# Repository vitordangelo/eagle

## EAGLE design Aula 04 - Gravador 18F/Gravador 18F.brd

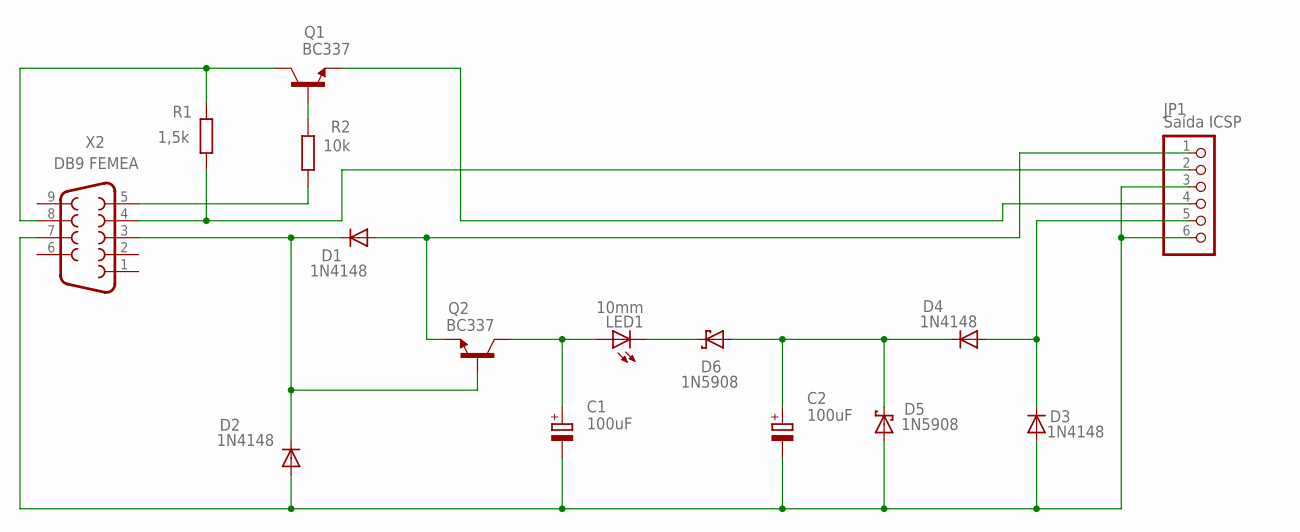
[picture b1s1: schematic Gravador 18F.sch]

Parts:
C1, C2: 100uF; E3,5-10
D1, D2, D3, D4: 1N4148; DO35-7
D5, D6: 1N5908; C4111-15
JP1: Saída ICSP; 1X06
LED1: 10mm; LED10MM
Q1, Q2: BC337; TO92
R1: 1,5k; 0207/7
R2: 10k; 0207/7
X2: DB9 FEMEA; F09HP

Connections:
unnamed: Q1.3 (C), R1.2, X2.8
unnamed: JP1.2, R1.1, X2.4
unnamed: Q1.2 (B), R2.2
unnamed: R2.1, X2.5
unnamed: C1.-, C2.-, D2.A, D3.A, D5.A, JP1.3, JP1.6, X2.7
unnamed: D1.C, D2.C, Q2.2 (B), X2.3
unnamed: C1.+, LED1.A, Q2.3 (C)
unnamed: D1.A, JP1.1, Q2.1 (E)
unnamed: D6.C, LED1.K (C)
unnamed: C2.+, D4.C, D5.C, D6.A
unnamed: D3.C, D4.A, JP1.5
unnamed: JP1.4, Q1.1 (E)

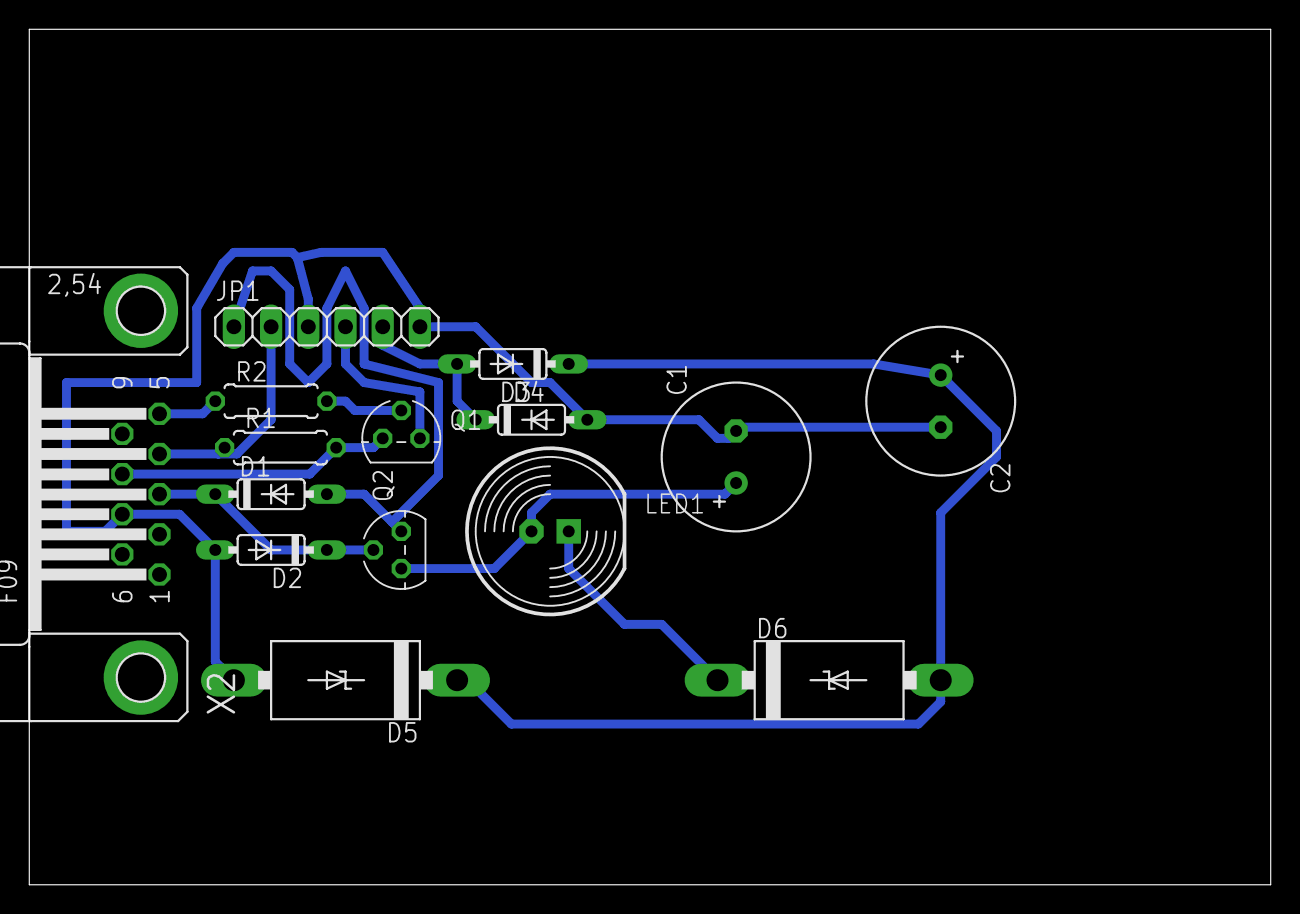
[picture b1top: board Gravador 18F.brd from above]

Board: 2 copper layers, 84.8 x 58.4 mm, 15 parts (0 on the bottom side), 12 nets.

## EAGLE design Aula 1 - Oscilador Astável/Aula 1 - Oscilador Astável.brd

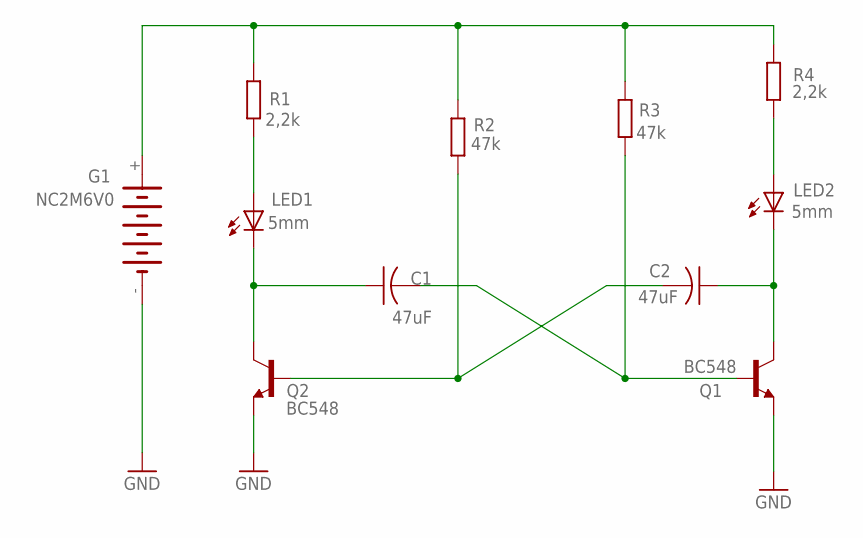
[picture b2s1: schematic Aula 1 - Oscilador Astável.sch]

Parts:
C1, C2: 47uF; C025-025X050
G1: NC2M6V0; NC2M
LED1, LED2: 5mm; LED5MM
Q1, Q2: BC548; TO92-EBC
R1, R4: 2,2k; 0204/5
R2, R3: 47k; 0204/5

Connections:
GND: G1.-, Q1.E, Q2.E
unnamed: LED1.A, R1.1
unnamed: G1.+, R1.2, R2.2, R3.2, R4.2
unnamed: LED2.A, R4.1
unnamed: C1.1, LED1.K (C), Q2.C
unnamed: C2.1, LED2.K (C), Q1.C
unnamed: C2.2, Q2.B, R2.1
unnamed: C1.2, Q1.B, R3.1

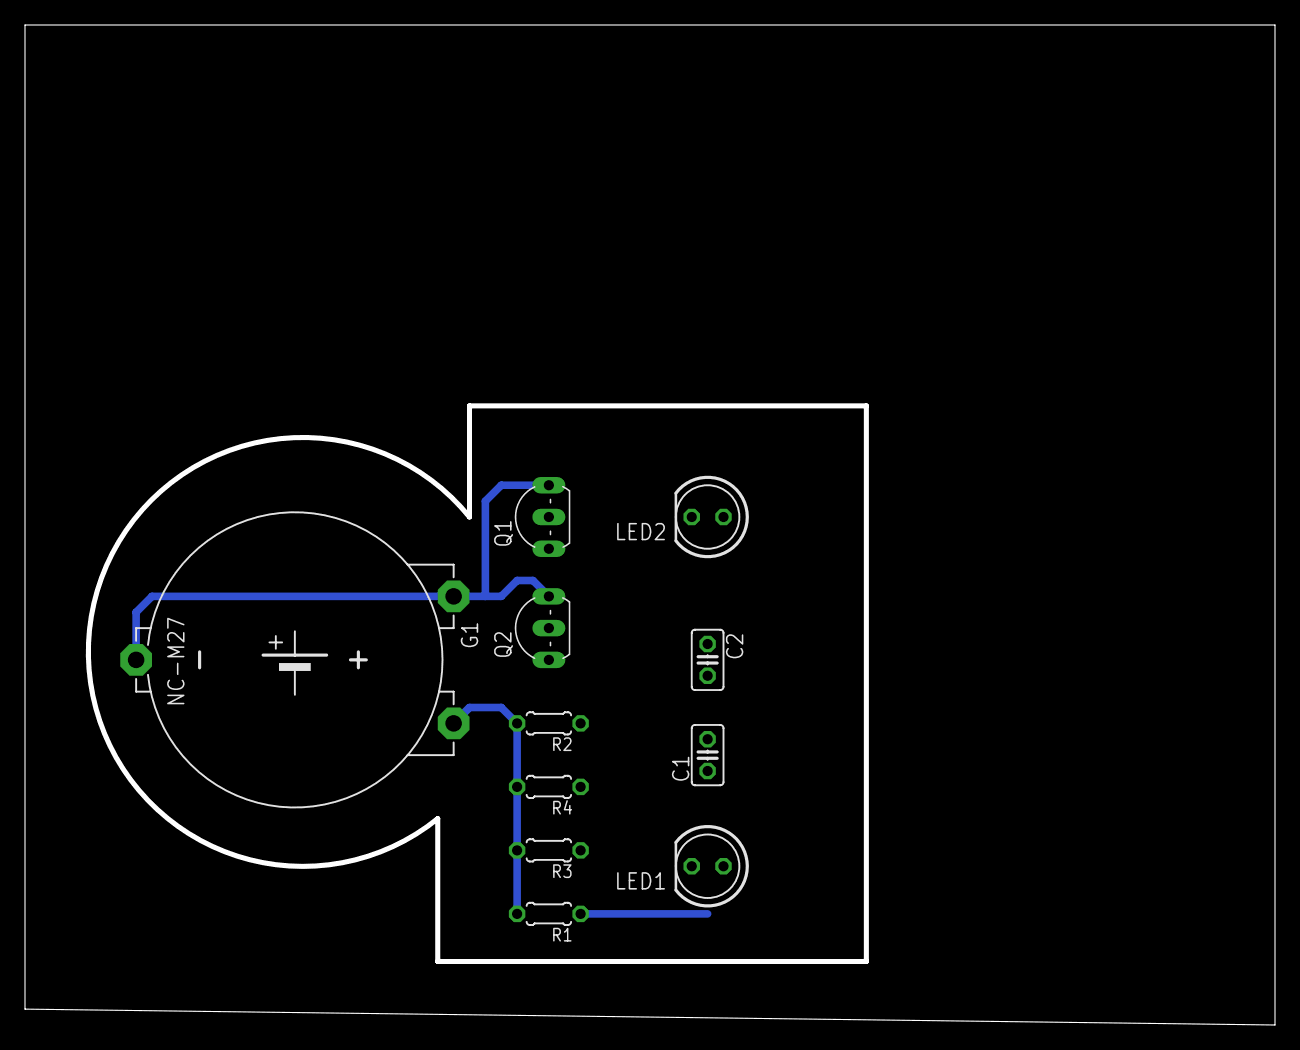
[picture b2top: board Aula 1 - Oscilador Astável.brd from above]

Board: 2 copper layers, 100.0 x 80.0 mm, 11 parts (0 on the bottom side), 8 nets.

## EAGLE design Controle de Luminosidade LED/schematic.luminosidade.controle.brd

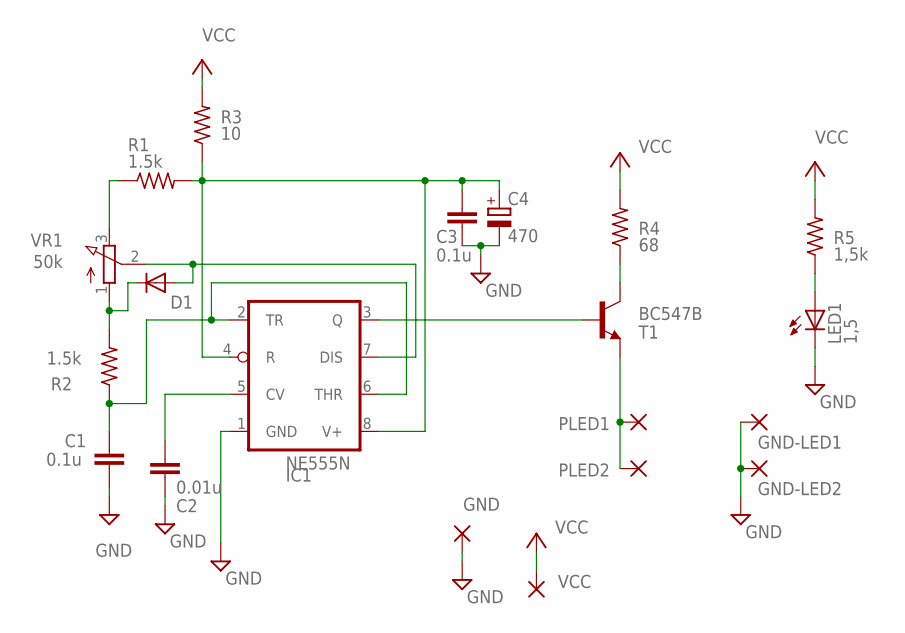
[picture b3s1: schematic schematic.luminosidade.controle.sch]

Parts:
C1, C3: 0.1u; C025-024X044
C2: 0.01u; C025-024X044
C4: 470; E3,5-10
D1: 1N4148DO35-7; DO35-7
GND: ET1; 2,15/1,0
GND-LED1, GND-LED2: GPAD; 2,15/1,0
IC1: NE555N; DIL08
LED1: 1,5; LED5MM
PLED1, PLED2: ET1; 2,15/1,0
R1, R2: 1.5k; 0204/5
R3: 10; 0204/5
R4: 68; 0204/5
R5: 1,5k; 0204/5
T1: BC547B; TO92
VCC: ET1; 2,15/1,0
VR1: 50k; 3RP/1610N

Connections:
GND: C1.2, C2.2, C3.2, C4.-, GND.1, GND-LED1.1, GND-LED2.1, IC1.1 (GND), LED1.K (C)
unnamed: C1.1, IC1.2 (TR), IC1.6 (THR), R2.1
unnamed: D1.C, R2.2, VR1.1 (A)
unnamed: D1.A, IC1.7 (DIS), VR1.2 (S)
unnamed: C2.1, IC1.5 (CV)
unnamed: R1.1, VR1.3 (E)
unnamed: IC1.3 (Q), T1.2 (B)
unnamed: C3.1, C4.+, IC1.4 (R), IC1.8 (V+), R1.2, R3.1
unnamed: R4.1, T1.3 (C)
unnamed: LED1.A, R5.1
unnamed: PLED1.1, PLED2.1, T1.1 (E)
VCC: R3.2, R4.2, R5.2, VCC.1

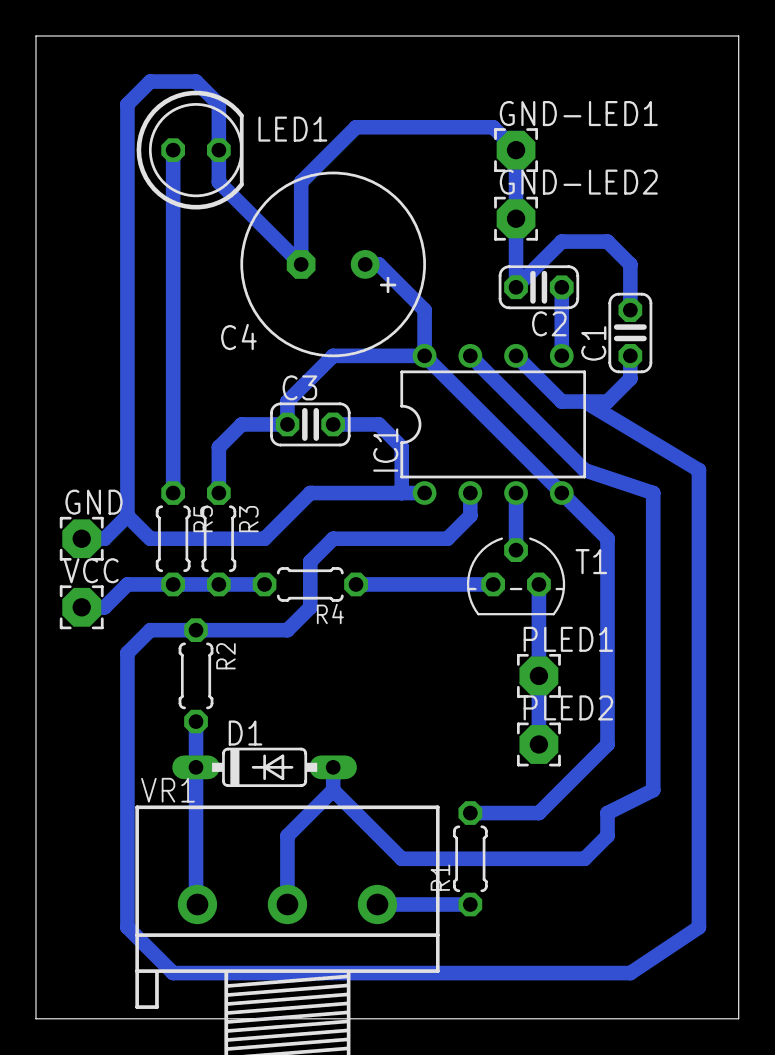
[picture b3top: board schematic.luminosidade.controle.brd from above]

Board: 2 copper layers, 39.0 x 54.6 mm, 20 parts (0 on the bottom side), 12 nets.
